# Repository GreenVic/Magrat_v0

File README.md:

# "Magrat" STM32H7 Board

NOTE: This is an early revision of a board which I am in the process of revising. I'm publishing the design files for the sake of sharing now that I've tested many (but not all) of the board's main features, but there are plenty of improvements which should be made, and you should not treat this as a solid reference implementation or a finalized production-ready design.

In particular, the SDRAM traces need better length- and impedance-matching; they seem to work up to 80-100MHz, but the chips are rated for 166MHz. The BOOT0 and JTAG signals should also be broken out, because the STM32H7's myriad clock domains seem to cause minor issues with SWD debugging.

With those disclaimers out of the way, "Magrat" is an STM32H7 board which aims to integrate enough external memory to run a minimal Linux system in a low-cost format. It is designed for single-sided PCA with parts from the LCSC catalog, so you should be able to order it 'as is' from JLCPCB when / if the parts are in stock.

This board should be able to run a mainline Linux kernel, and I've gotten one booting, but I'm still working on bringing up a fully-functional system, and I'm not quite sure that the microSD card socket works yet.

(TODO: add generated gerbers, BoM, pick-and-place files)

# Board Renders:

## Features

* STM32H7x3II: Cortex-M7, 480MHz, 2MiB Flash, 1MiB RAM

* 32MiB SDRAM

* 16MiB Quad-SPI Flash

* 50-pin ILI9341 display connector (untested)

* USB full-speed (untested)

* microSD card socket (untested)

* UART, SPI, I2C headers.

## (TODO: more explanation)

Test programs and a bit more information can be found in the `firmware/` directory.

They're a little rough-around-the-edges right now, because I haven't had these boards for long and it's my first time using an STM32H7 chip.

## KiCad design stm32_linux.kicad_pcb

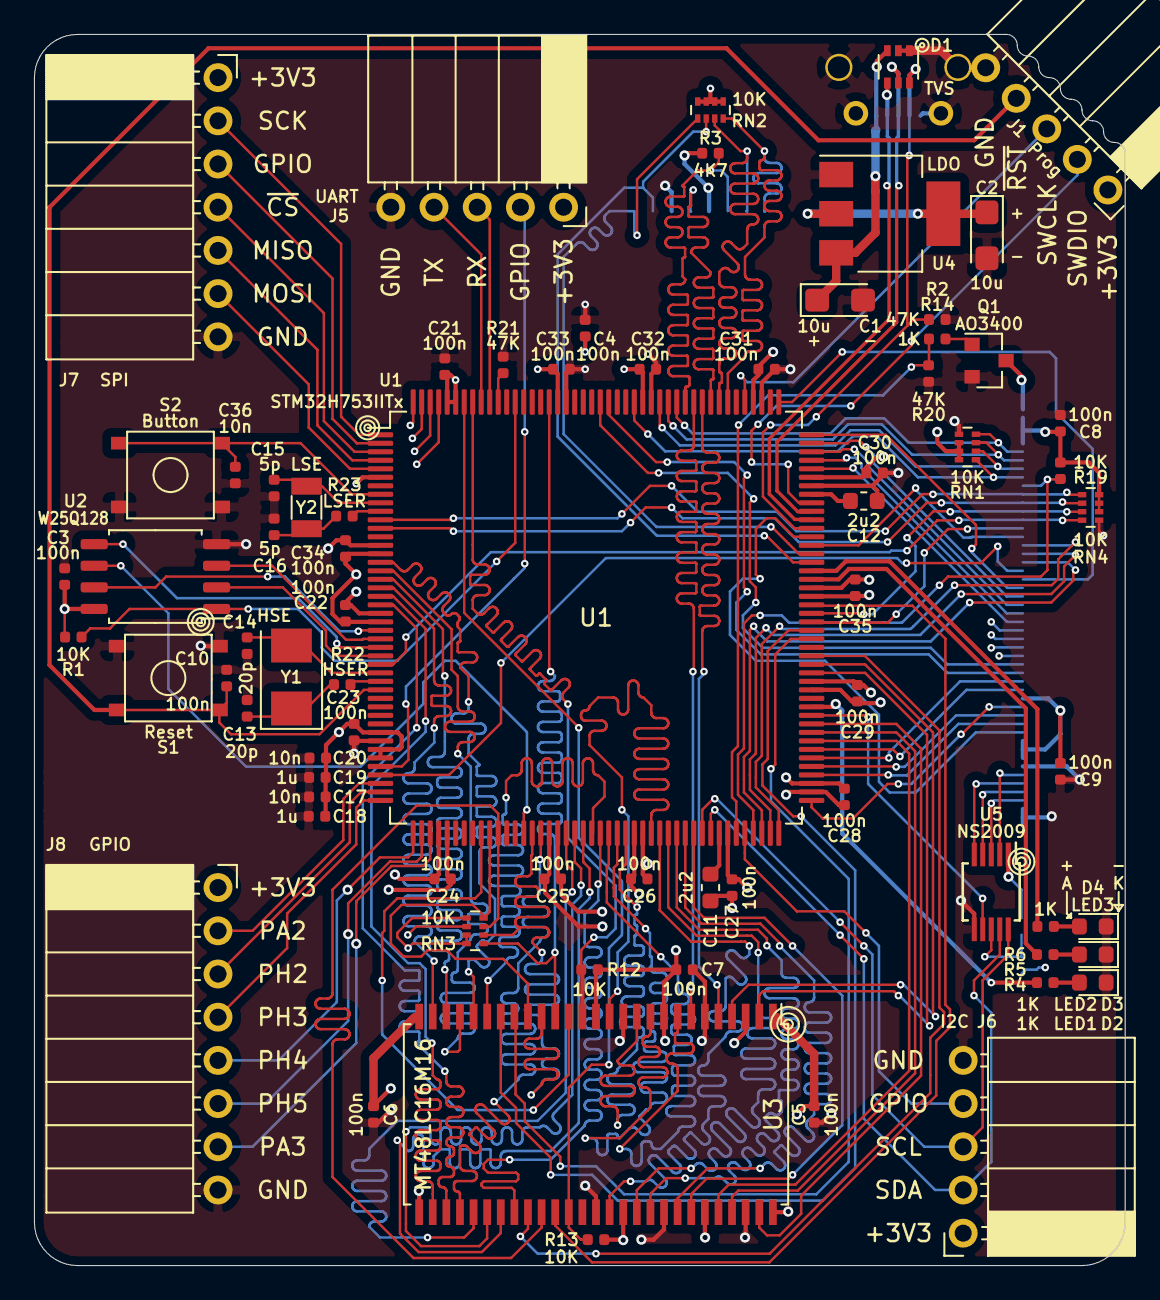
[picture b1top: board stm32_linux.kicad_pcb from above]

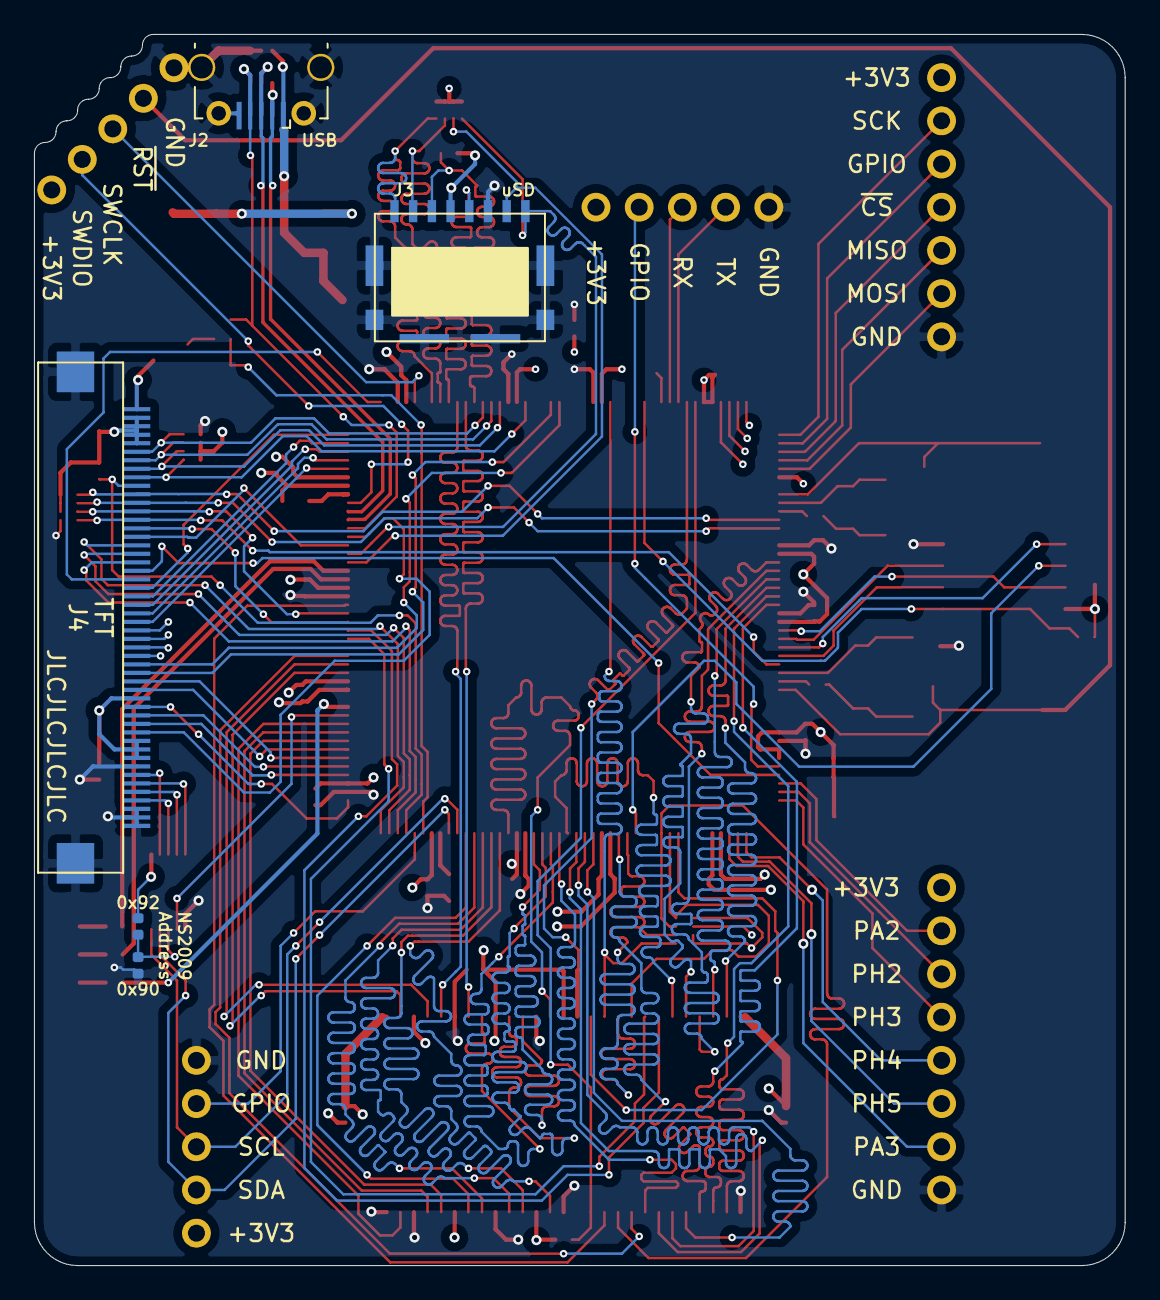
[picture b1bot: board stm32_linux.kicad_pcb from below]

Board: 4 copper layers, 64.1 x 72.4 mm, 78 parts (5 on the bottom side), 135 nets.

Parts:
C1, C2: 10u; CP_EIA-3216-10_Kemet-I
C3, C4, C5, C6, C7, C8, C9, C10, C21, C22, C23, C24, C25, C26, C27, C28, C29, C30, C31, C32, C33, C34, C35: 100n; C_0402_1005Metric
C11, C12: 2u2; C_0603_1608Metric
C13, C14: 20p; C_0402_1005Metric
C15, C16: 5p; C_0402_1005Metric
C17, C20, C36: 10n; C_0402_1005Metric
C18, C19: 1u; C_0402_1005Metric
D1: TVS; SOT-363_SC-70-6
D2: LED1; LED_0603_1608Metric
D3: LED2; LED_0603_1608Metric
D4: LED3; LED_0603_1608Metric
J1: Prog; PinSocket_1x05_P2.54mm_Horizontal
J2: USB; MyMicroUSB
J3: uSD; microSD_1051620001
J4: TFT; FPC_50p_0.5mm
J5: UART; PinSocket_1x05_P2.54mm_Horizontal
J6: I2C; PinSocket_1x05_P2.54mm_Horizontal
J7: SPI; PinSocket_1x07_P2.54mm_Horizontal
J8: GPIO; PinSocket_1x08_P2.54mm_Horizontal
Q1: AO3400; SOT-23
R1, R12, R13, R19: 10K; R_0402_1005Metric
R2, R20, R21: 47K; R_0402_1005Metric
R3: 4K7; R_0402_1005Metric
R4, R5, R6, R14: 1K; R_0402_1005Metric
R7: 0x92; R_0402_1005Metric
R8: 0x90; R_0402_1005Metric
R22: HSER; R_0402_1005Metric
R23: LSER; R_0402_1005Metric
RN1, RN2, RN3, RN4: 10K; R_Array_Concave_4x0402
S1: Reset; button_jlcpcb
S2: Button; button_jlcpcb
U1: STM32H753IITx; LQFP-176_24x24mm_P0.5mm
U2: W25Q128; SOIC-8_5.23x5.23mm_P1.27mm
U3: MT48LC16M16; TSOP-II-54_22.2x10.16mm_P0.8mm
U4: LDO; SOT-223-3_TabPin2
U5: NS2009; MSOP-10_3x3mm_P0.5mm
Y1: HSE; Crystal_SMD_5032-2Pin_5.0x3.2mm
Y2: LSE; Crystal_SMD_3215-2Pin_3.2x1.5mm

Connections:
+3V3: C2.1, C3.1, C4.1, C5.2, C6.2, C7.2, C8.1, C9.1, C17.2, C18.2, C19.2, C20.2, C21.2, C22.2, C23.2, C24.2, C25.2, C26.2, C27.2, C28.2, C29.2, C30.2, C31.2, C32.2, C33.2, C34.2, C35.2, J1.1, J3.4, J4.2, J4.3, J4.4, J4.5, J4.35, J4.40, J4.41, J4.42, J5.1, J6.1, J7.1, J8.1, R1.1, R3.1, R7.1, R12.2, R13.2, R19.1, RN1.2, RN1.3, RN1.4, RN2.5, RN2.6, RN2.7, RN2.8, RN3.5, RN3.7, RN3.8, RN4.6, RN4.7, RN4.8, U1.6, U1.15, U1.23, U1.36, U1.38, U1.39, U1.49, U1.62, U1.72, U1.82, U1.91, U1.103, U1.114, U1.127, U1.136, U1.149, U1.159, U1.171, U1.172, U2.8, U3.1, U3.3, U3.9, U3.14, U3.27, U3.43, U3.49, U4.2, U5.1
+5V: C1.1, D1.3, J2.1, U4.3
BTN1: C36.2, S2.1, U1.8
FMC_A0: U1.16, U3.23
FMC_A1: U1.17, U3.24
FMC_A2: U1.18, U3.25
FMC_A3: U1.19, U3.26
FMC_A4: U1.20, U3.29
FMC_A5: U1.21, U3.30
FMC_A6: U1.60, U3.31
FMC_A7: U1.63, U3.32
FMC_A8: U1.64, U3.33
FMC_A9: U1.65, U3.34
FMC_A10: U1.66, U3.22
FMC_A11: U1.67, U3.35
FMC_A12: U1.106, U3.36
FMC_BA0: U1.108, U3.20
FMC_BA1: U1.109, U3.21
FMC_D0: U1.104, U3.2
FMC_D1: U1.105, U3.4
FMC_D2: U1.142, U3.5
FMC_D3: U1.143, U3.7
FMC_D4: U1.68, U3.8
FMC_D5: U1.69, U3.10
FMC_D6: U1.70, U3.11
FMC_D7: U1.73, U3.13
FMC_D8: U1.74, U3.42
FMC_D9: U1.75, U3.44
FMC_D10: U1.76, U3.45
FMC_D11: U1.77, U3.47
FMC_D12: U1.78, U3.48
FMC_D13: U1.96, U3.50
FMC_D14: U1.97, U3.51
FMC_D15: U1.98, U3.53
FMC_NBL0: R12.1, U1.169, U3.15
FMC_NBL1: R13.1, U1.170, U3.39
FMC_NCAS: RN3.1, U1.160, U3.17
FMC_NRAS: RN3.2, U1.59, U3.18
FMC_SDCKE0: RN3.3, U1.55, U3.37
FMC_SDCLK: U1.112, U3.38
FMC_SDNE0: RN3.4, U1.54, U3.19
FMC_SDNWE: U1.53, U3.16
GND: C1.2, C2.2, C3.2, C4.2, C5.1, C6.1, C7.1, C8.2, C9.2, C10.2, C11.2, C12.2, C13.2, C14.1, C15.1, C16.1, C17.1, C18.1, C19.1, C20.1, C21.1, C22.1, C23.1, C24.1, C25.1, C26.1, C27.1, C28.1, C29.1, C30.1, C31.1, C32.1, C33.1, C34.1, C35.1, C36.1, D1.1, D1.2, D2.1, D3.1, D4.1, J1.5, J2.5, J2.6, J3.6, J3.9, J4.43, J4.48, J4.49, J4.50, J4.51, J5.5, J6.5, J7.7, J8.8, Q1.2, R2.1, R8.2, R20.2, R21.2, RN1.1, RN3.6, RN4.5, S1.1, S2.2, U1.14, U1.22, U1.37, U1.48, U1.61, U1.71, U1.90, U1.102, U1.113, U1.126, U1.135, U1.148, U1.158, U2.4, U3.6, U3.12, U3.28, U3.41, U3.46, U3.52, U3.54, U4.1, U5.6
I2C_ETC: J6.4, U1.84
I2C_SCL: J6.3, U1.79, U5.10
I2C_SDA: J6.2, U1.80, U5.9
LED1: R4.2, U1.100
LED2: R5.2, U1.115
LED3: R6.2, U1.116
MMC_CLK: J3.5, U1.141
MMC_CMD: J3.3, R3.2, U1.144
MMC_D0: J3.7, RN2.2, U1.117
MMC_D1: J3.8, RN2.1, U1.118
MMC_D2: J3.1, RN2.4, U1.139
MMC_D3: J3.2, RN2.3, U1.140
unnamed: C11.1, U1.81
unnamed: C12.1, U1.125
unnamed: C13.1, R22.2, Y1.1
unnamed: C14.2, U1.29, Y1.2
unnamed: C15.2, U1.9, Y2.1
unnamed: C16.2, R23.1, Y2.2
unnamed: D2.2, R4.1
unnamed: D3.2, R5.1
unnamed: D4.2, R6.1
unnamed: J4.1, Q1.3
unnamed: Q1.1, R14.1
unnamed: R7.2, R8.1, U5.8
unnamed: R21.1, U1.166
unnamed: R22.1, U1.30
unnamed: R23.2, U1.10
PA2: J8.2, U1.42
PA3: J8.7, U1.47
PH2: J8.3, U1.43
PH3: J8.4, U1.44
PH4: J8.5, U1.45
PH5: J8.6, U1.46
QSPI_CLK: U1.58, U2.6
QSPI_D0: U1.26, U2.5
QSPI_D1: U1.27, U2.2
QSPI_D2: U1.25, U2.3
QSPI_D3: U1.24, U2.7
QSPI_~CS: R1.2, U1.164, U2.1
RST: C10.1, J1.4, S1.2, U1.31
SPI_ETC: J7.3, U1.2
SPI_MISO: J7.5, U1.4
SPI_MOSI: J7.6, U1.5
SPI_SCK: J7.2, U1.1
SPI_~CS: J7.4, U1.3
SWCLK: J1.3, U1.137
SWDIO: J1.2, U1.124
TFT_B2: J4.32, U1.153
TFT_B3: J4.31, U1.154
TFT_B4: J4.30, U1.173
TFT_B5: J4.29, U1.174
TFT_B6: J4.28, U1.175
TFT_B7: J4.27, U1.176
TFT_D6: J4.26, U1.128
TFT_D7: J4.25, U1.129
TFT_D8: J4.24, U1.130
TFT_D9: J4.23, U1.131
TFT_D10: J4.22, U1.132
TFT_D11: J4.21, U1.133
TFT_D12: J4.20, U1.41
TFT_D13: J4.19, U1.86
TFT_D14: J4.18, U1.87
TFT_D15: J4.17, U1.88
TFT_D16: J4.16, U1.119
TFT_D17: J4.15, U1.110
TFT_DC: J4.36, U1.89
TFT_DE: J4.14, RN4.4, U1.28
TFT_DOTCLK: J4.13, RN4.3, U1.111
TFT_HSYNC: J4.12, RN4.2, U1.12
TFT_IM0: J4.6, RN1.8, U1.145
TFT_IM1: J4.7, RN1.7, U1.146
TFT_IM2: J4.8, RN1.6, U1.147
TFT_IM3: J4.9, RN1.5, U1.150
TFT_MISO: J4.33, U1.94
TFT_MOSI: J4.34, U1.95
TFT_PWM: R14.2, R20.1, U1.83
TFT_RST: J4.10, R19.2, U1.85
TFT_SCK: J4.37, U1.93
TFT_TE: J4.39, U1.120
TFT_VSYNC: J4.11, RN4.1, U1.11
TFT_XL: J4.46, U5.4
TFT_XR: J4.44, U5.2
TFT_YD: J4.45, U5.5
TFT_YU: J4.47, U5.3
TFT_~CS: J4.38, U1.92
TIRQ: U1.99, U5.7
UART_ETC: J5.2, U1.40
UART_RX: J5.3, U1.167
UART_TX: J5.4, U1.168
USB_D+: D1.5, J2.3, U1.123
USB_D-: D1.4, J2.2, U1.122
USB_ID: D1.6, J2.4, R2.2, U1.121

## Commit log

2020-10-01 Initial project files: rev0.
2020-10-01 Add firmware directory and readme
2020-10-01 Add common supporting files for test firmwares.
2020-10-01 Add LED test firmware
2020-10-01 Add button test firmware
2020-10-01 Add directories for unfinished SD/MMC and oscillator tests.
2020-10-01 Add QSPI Flash test program.
2020-10-01 Add UART test program.
2020-10-01 Add SDRAM test program.
2020-10-01 Add WIP Linux bootloader for the board.
2020-10-01 Clarify readme
2020-10-01 Add renders of the board top / bottom
2020-10-01 Readme: add a couple of specific issues with the design
